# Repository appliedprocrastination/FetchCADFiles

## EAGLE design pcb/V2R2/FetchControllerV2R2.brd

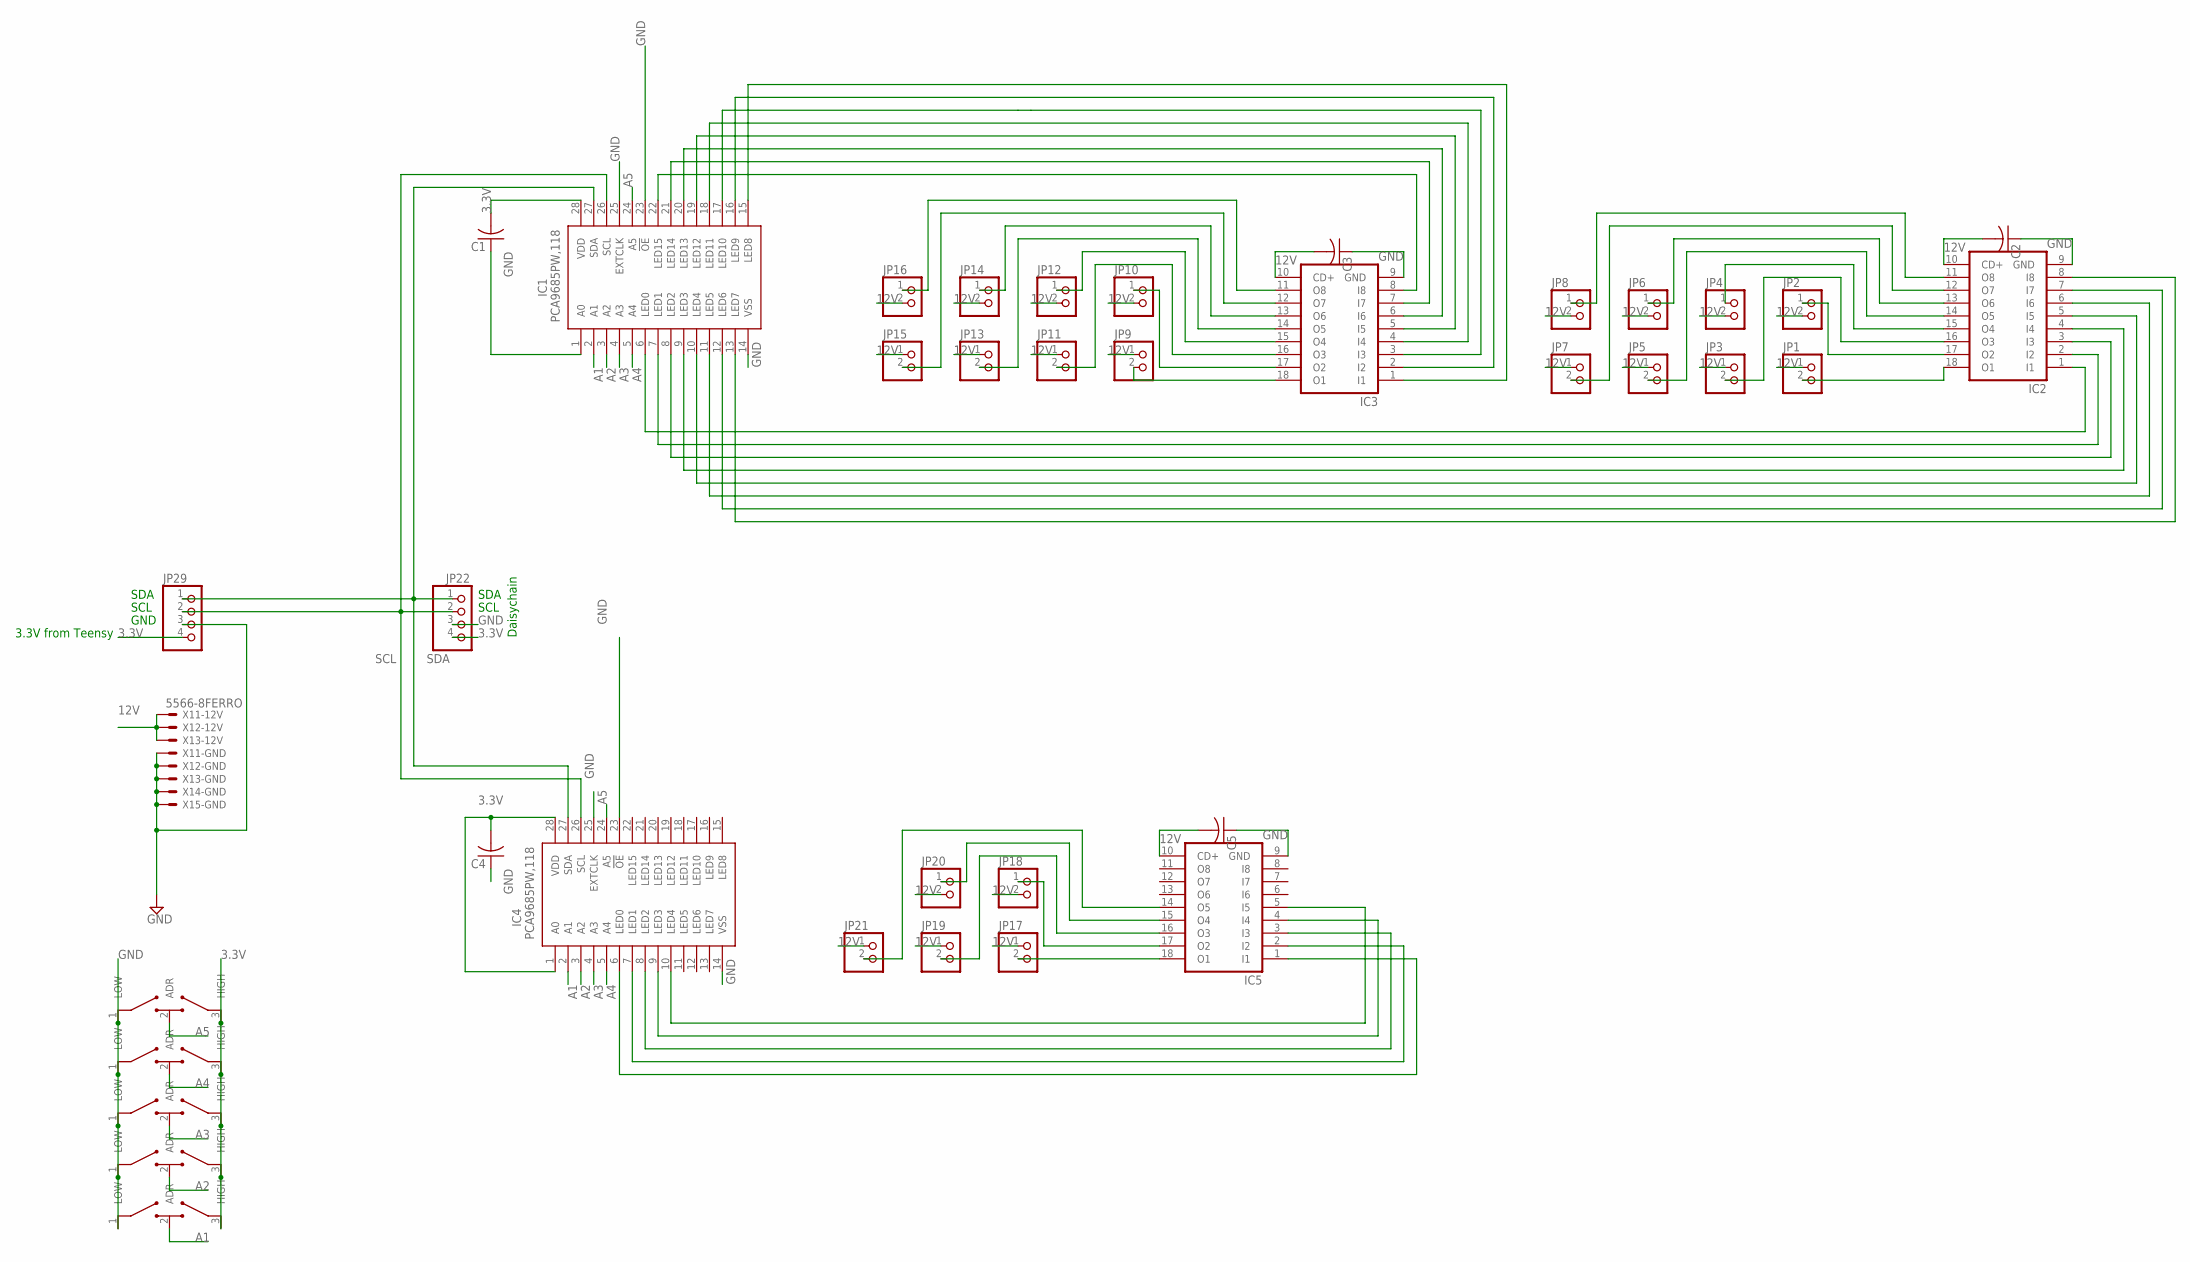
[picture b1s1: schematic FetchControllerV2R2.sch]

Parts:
C1, C2, C3, C4, C5: C-USC0603; C0603
IC1, IC4: PCA9685PW,118; SOP65P640X110-28N
IC2, IC3, IC5: ULN2803ASMT; SO18W
JP1, JP3, JP5, JP7, JP9, JP11, JP13, JP15, JP17, JP19, JP21: PINHD-1X2SOLENOID-R; SOLENOID-CONTACT-REVERSE
JP2, JP4, JP6, JP8, JP10, JP12, JP14, JP16, JP18, JP20: PINHD-1X2SOLENOID; SOLENOID-CONTACT
JP22, JP29: PINHD-1X4; 1X04
U$1, U$2, U$3, U$4, U$5: ADR-SELECT; ADR-SELECT-SOLDER
X1: 5566-8FERRO; 5566-8-CLEAN

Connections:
3.3V: C1.2, C4.2, IC1.28 (VDD), IC4.1 (A0), IC4.28 (VDD), JP22.4, JP29.4, U$1.3 (HIGH), U$2.3 (HIGH), U$3.3 (HIGH), U$4.3 (HIGH), U$5.3 (HIGH)
12V: C2.2, C3.2, C5.2, IC2.10 (CD+), IC3.10 (CD+), IC5.10 (CD+), JP1.1, JP2.2, JP3.1, JP4.2, JP5.1, JP6.2, JP7.1, JP8.2, JP9.1, JP10.2, JP11.1, JP12.2, JP13.1, JP14.2, JP15.1, JP16.2, JP17.1, JP18.2, JP19.1, JP20.2, JP21.1, X1.1, X1.2, X1.3
A1: IC1.2 (A1), IC4.2 (A1), U$5.2 (ADR)
A2: IC1.3 (A2), IC4.3 (A2), U$4.2 (ADR)
A3: IC1.4 (A3), IC4.4 (A3), U$3.2 (ADR)
A4: IC1.5 (A4), IC4.5 (A4), U$2.2 (ADR)
A5: IC1.24 (A5), IC4.24 (A5), U$1.2 (ADR)
GND: C1.1, C2.1, C3.1, C4.1, C5.1, IC1.1 (A0), IC1.14 (VSS), IC1.23 (!OE), IC1.25 (EXTCLK), IC2.9 (GND), IC3.9 (GND), IC4.14 (VSS), IC4.23 (!OE), IC4.25 (EXTCLK), IC5.9 (GND), JP22.3, JP29.3, U$1.1 (LOW), U$2.1 (LOW), U$3.1 (LOW), U$4.1 (LOW), U$5.1 (LOW), X1.4, X1.5, X1.6, X1.7, X1.8
unnamed: IC2.18 (O1), JP1.2
unnamed: IC1.13 (LED7), IC2.8 (I8)
unnamed: IC4.7 (LED1), IC5.2 (I2)
unnamed: IC2.17 (O2), JP2.1
unnamed: IC2.16 (O3), JP3.2
unnamed: IC4.9 (LED3), IC5.4 (I4)
unnamed: IC2.15 (O4), JP4.1
unnamed: IC2.14 (O5), JP5.2
unnamed: IC2.13 (O6), JP6.1
unnamed: IC2.12 (O7), JP7.2
unnamed: IC2.11 (O8), JP8.1
unnamed: IC3.18 (O1), JP9.2
unnamed: IC3.17 (O2), JP10.1
unnamed: IC3.16 (O3), JP11.2
unnamed: IC3.15 (O4), JP12.1
unnamed: IC3.14 (O5), JP13.2
unnamed: IC3.13 (O6), JP14.1
unnamed: IC3.12 (O7), JP15.2
unnamed: IC3.11 (O8), JP16.1
unnamed: IC4.6 (LED0), IC5.1 (I1)
unnamed: IC4.8 (LED2), IC5.3 (I3)
unnamed: IC4.10 (LED4), IC5.5 (I5)
unnamed: IC5.18 (O1), JP17.2
unnamed: IC5.17 (O2), JP18.1
unnamed: IC5.16 (O3), JP19.2
unnamed: IC5.15 (O4), JP20.1
unnamed: IC5.14 (O5), JP21.2
unnamed: IC1.6 (LED0), IC2.1 (I1)
unnamed: IC1.8 (LED2), IC2.3 (I3)
unnamed: IC1.10 (LED4), IC2.5 (I5)
unnamed: IC1.12 (LED6), IC2.7 (I7)
unnamed: IC1.15 (LED8), IC3.1 (I1)
unnamed: IC1.16 (LED9), IC3.2 (I2)
unnamed: IC1.17 (LED10), IC3.3 (I3)
unnamed: IC1.18 (LED11), IC3.4 (I4)
unnamed: IC1.19 (LED12), IC3.5 (I5)
unnamed: IC1.20 (LED13), IC3.6 (I6)
unnamed: IC1.21 (LED14), IC3.7 (I7)
unnamed: IC1.22 (LED15), IC3.8 (I8)
unnamed: IC1.11 (LED5), IC2.6 (I6)
unnamed: IC1.9 (LED3), IC2.4 (I4)
unnamed: IC1.7 (LED1), IC2.2 (I2)
SCL: IC1.26 (SCL), IC4.26 (SCL), JP22.2, JP29.2
SDA: IC1.27 (SDA), IC4.27 (SDA), JP22.1, JP29.1

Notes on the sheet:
GND
SCL
SDA
3.3V from Teensy
Daisychain

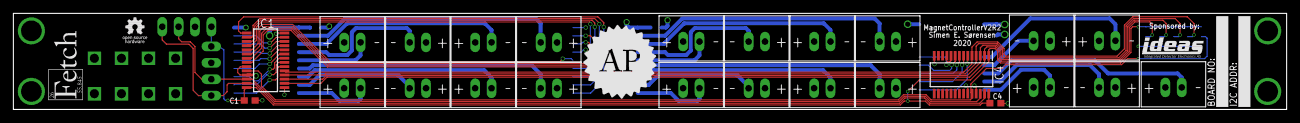
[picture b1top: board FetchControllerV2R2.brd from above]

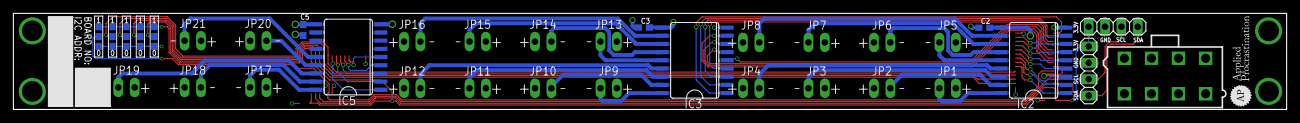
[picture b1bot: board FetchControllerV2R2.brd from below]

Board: 4 copper layers, 197.5 x 14.9 mm, 44 parts (15 on the bottom side), 52 nets.

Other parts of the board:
U$6: APPLIED-PROC
U$7: FETCH
U$8: APPLIED-PROCRASTINATION-FULL-SMALL
U$9: IDEAS-LOGO-SMALL
U$10: OSHW-LOGO

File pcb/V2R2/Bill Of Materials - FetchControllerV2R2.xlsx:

Qty | Value | Device | Package | Parts | Description | DESCRIPTION.1 | HEIGHT | MANUFACTURER_NAME | MANUFACTURER_PART_NUMBER | MOUSER_PART_NUMBER | MOUSER_PRICE-STOCK | Column1
5 |  | C-USC0603 | C0603 | C1, C2, C3, C4, C5 | CAPACITOR, American symbol |  |  | Generic
21 |  | PINHD-1X2SOLENOID | SOLENOID-CONTACT | JP1, JP3, JP5, JP7, JP9, JP11, JP13, JP15, JP17, JP19, JP21, JP2, JP4, JP6, JP8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 | PIN HEADER |  |  | Generic 2.54mm pitch
2 |  | PINHD-1X4 | 1X04 | JP22, JP29 | PIN HEADER |  |  | Generic 2.54mm pitch
3 |  | ULN2803ASMT | SO18W | IC2, IC3, IC5 | DRIVER ARRAY |  |  | Texas Instruments
1 | 5566-8 | 5566-8 | 5566-8 | X1 | Molex Mini FIT connector 8 pol |  |  | Molex
2 | PCA9685PW,118 | PCA9685PW,118 | SOP65P640X110-28N | IC1, IC4 | LED Display Drivers | LED Display Drivers | 1.1mm | NXP | PCA9685PW,118 | 771-PCA9685PW,118 | https://www.mouser.com/Search/Refine.aspx?Keyword=771-PCA968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

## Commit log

2019-11-26 added 3d models
2019-11-26 added pcb files
2020-05-25 Exported BOM and Gerber
    Exported Gerber with default Eagle 2-layer settings and made a annotated .xlsx version of the BOM
2020-11-15 Untested PCBV2
    Added gerbers to a preliminary PCB V2. This has not been fully tested and validated yet and should not be used until a video about the PCB is published on YouTube.
2021-08-24 Added FetchControllerV2R2
    The FetchControllerV2R2 (also called MagnetController) has been verified to work and is therefore uploaded in full.
